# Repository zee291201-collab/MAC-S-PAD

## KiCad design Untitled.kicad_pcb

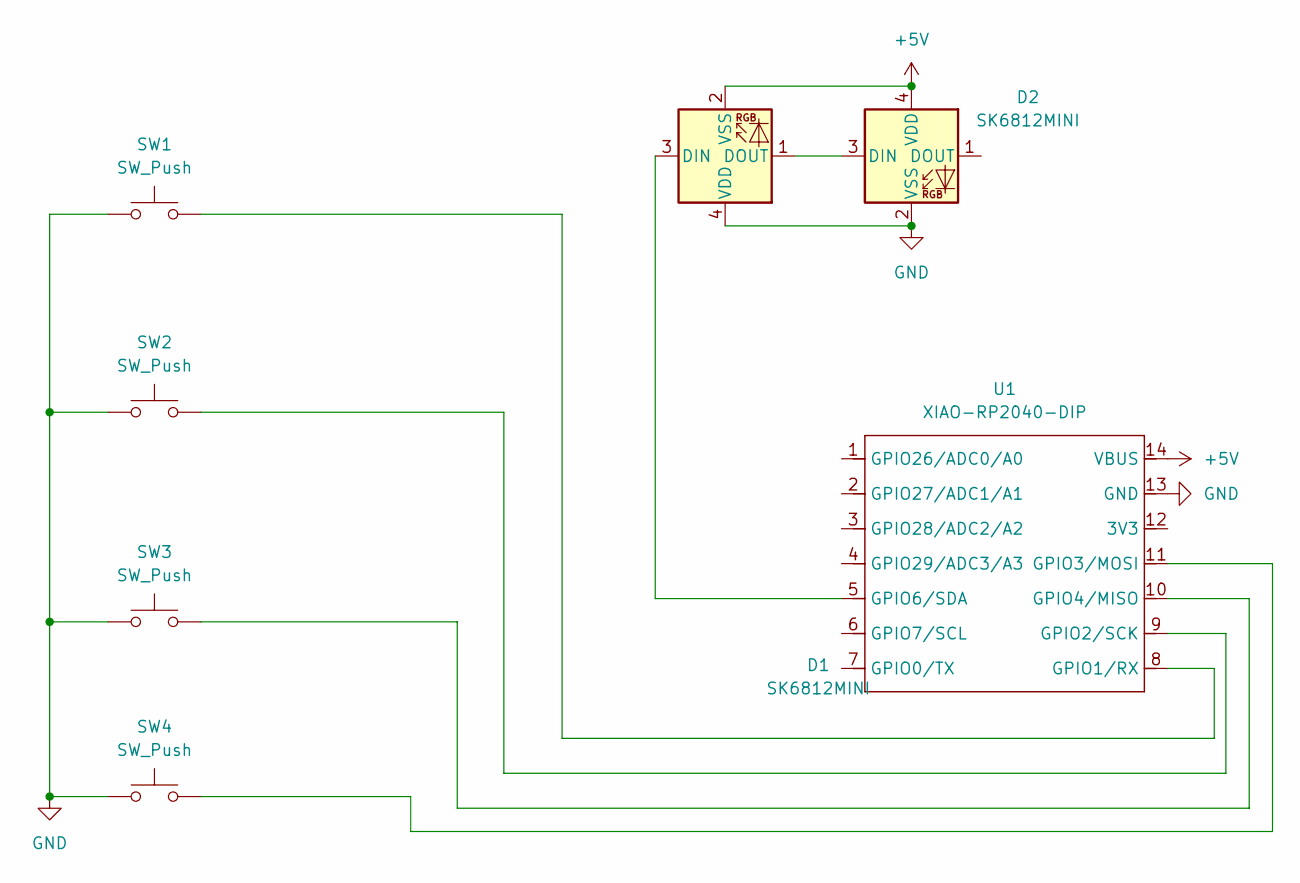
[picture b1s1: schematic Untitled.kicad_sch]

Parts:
D1, D2: SK6812MINI; LED_SK6812MINI_PLCC4_3.5x3.5mm_P1.75mm
SW1, SW2, SW3, SW4: SW_Push; SW_Cherry_MX_1.00u_PCB
U1: XIAO-RP2040-DIP; MCU_Seeed_ESP32C3

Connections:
+5V: D1.2 (VSS), D2.4 (VDD), U1.14 (VBUS)
GND: D1.4 (VDD), D2.2 (VSS), SW1.1, SW2.1, SW3.1, SW4.1, U1.13 (GND)
unnamed: D1.3 (DIN), U1.5 (GPIO6/SDA)
unnamed: D1.1 (DOUT), D2.3 (DIN)
unnamed: SW1.2, U1.8 (GPIO1/RX)
unnamed: SW2.2, U1.9 (GPIO2/SCK)
unnamed: SW4.2, U1.11 (GPIO3/MOSI)
unnamed: SW3.2, U1.10 (GPIO4/MISO)

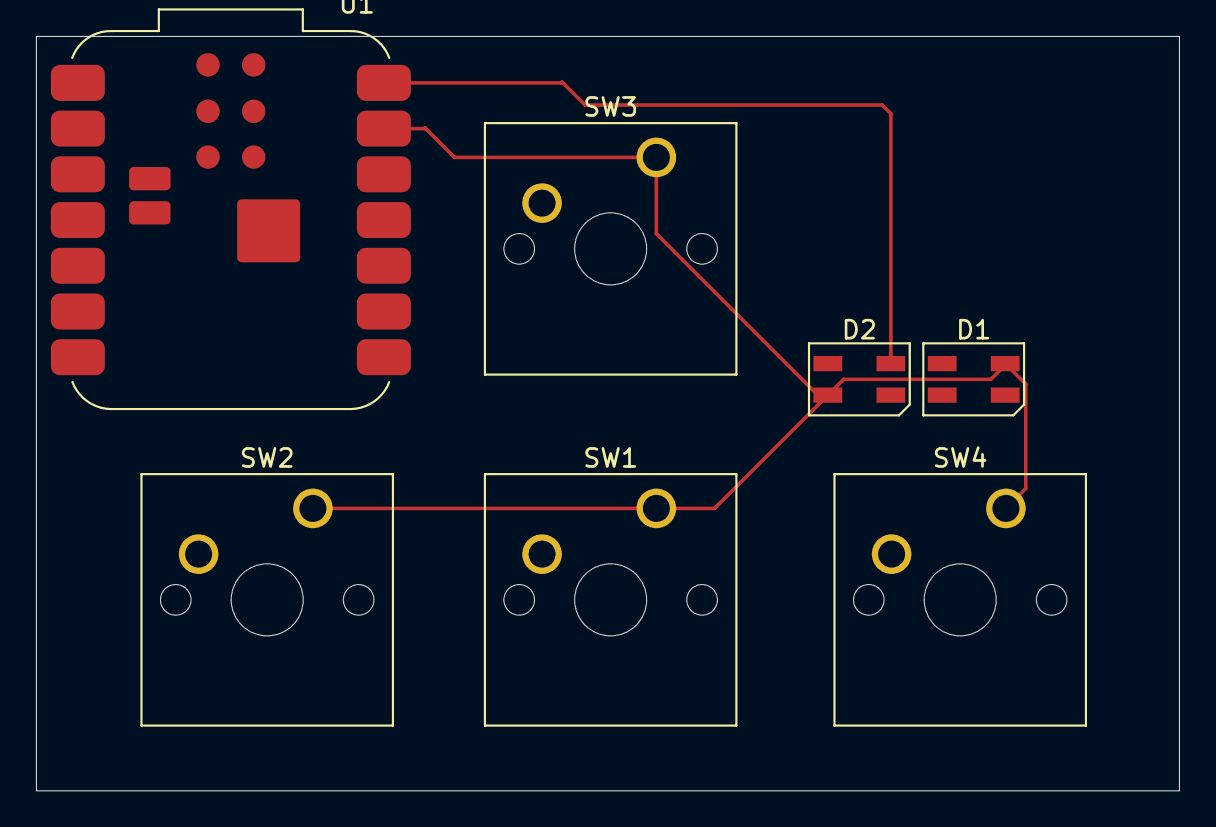
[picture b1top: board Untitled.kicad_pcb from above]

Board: 2 copper layers, 63.5 x 41.9 mm, 7 parts (0 on the bottom side), 8 nets.

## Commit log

2025-12-29 Add files via upload
    ALL OF THIS IS FOR THE HACKPAD WHICH UTILIZES FOUR KEYS- WASD
